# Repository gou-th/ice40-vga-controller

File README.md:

# ice40-vga-controller

A custom FPGA-based VGA controller designed for **640×480 @ 60 Hz**, implementing VGA timing generation, pixel logic and a **4-layer PCB** using the **Lattice iCE40HX1K** FPGA.

---

## Overview

This project implements a minimal yet fully functional VGA video controller without using vendor IP cores. The design follows a complete hardware development flow, starting from logic validation and RTL simulation to a manufacturable multilayer PCB.

The controller generates standard VGA sync signals and RGB video output compatible with conventional VGA displays.

---

## Architecture

The system is divided into three main functional blocks:

### VGA Timing Generation

* Horizontal and vertical pixel counters
* HSYNC and VSYNC pulse generation
* Active video region detection based on VGA timing parameters

### Pixel Generation

* RGB pixel values derived from current pixel coordinates
* Simple scrolling color-bar test pattern
* 4-bit color depth per RGB channel

### Hardware Output

* Digital RGB converted to analog VGA levels using a resistor ladder DAC
* Standard DE-15 VGA connector interface
* FPGA I/O powered at 3.3 V with proper decoupling

---

## Implementation Flow

### Logic Validation

Initial VGA timing was verified using Digital simulation software to confirm counter behavior, sync pulse timing and active display window alignment.

Reference: [`Digital`](./digital)

### RTL Design and Simulation

The design is implemented in SystemVerilog using a modular structure:

* [`vga_timing.sv`](./systemverilog/rtl/vga_timing.sv) – VGA timing and sync generation
* [`vga_pixel_gen.sv`](./systemverilog/rtl/vga_pixel_gen.sv) – RGB pixel generation
* [`vga_timing_tb.sv`](./systemverilog/sim/vga_timing_tb.sv) – Testbench for waveform-level verification

References:

* RTL: [`RTL`](./systemverilog/rtl)
* Simulation: [`Simulation & Waveform`](./systemverilog/sim)

### PCB Design

A complete 4-layer PCB was designed in KiCad to host the VGA controller.

Layer stackup:

* Top: Signal routing
* Inner 1: Ground plane
* Inner 2: Power planes
* Bottom: Signal routing

Key hardware features:

* Lattice iCE40HX1K FPGA
* Dedicated core and I/O power planes
* Local decoupling on all power pins
* VGA DAC placed close to FPGA outputs

References:

* Schematic:  [`Schematic`](./kicad/schematic)
* PCB: [`PCB`](./kicad/pcb)
* Gerbers: [`Gerber`](./kicad/gerber)

---

## 3D PCB View

---

### Folder Structure

<pre>
ice40-vga-controller/
├── digital/                # VGA timing validation using Digital simulation tool
├── systemverilog/
│   ├── rtl/                # SystemVerilog RTL source files
│   └── sim/                # Testbench and simulation files
├── kicad/
│   ├── schematic/          # Circuit schematics
│   ├── pcb/                # PCB layout files
│   └── gerber/             # Manufacturing Gerber files
└── README.md
</pre>

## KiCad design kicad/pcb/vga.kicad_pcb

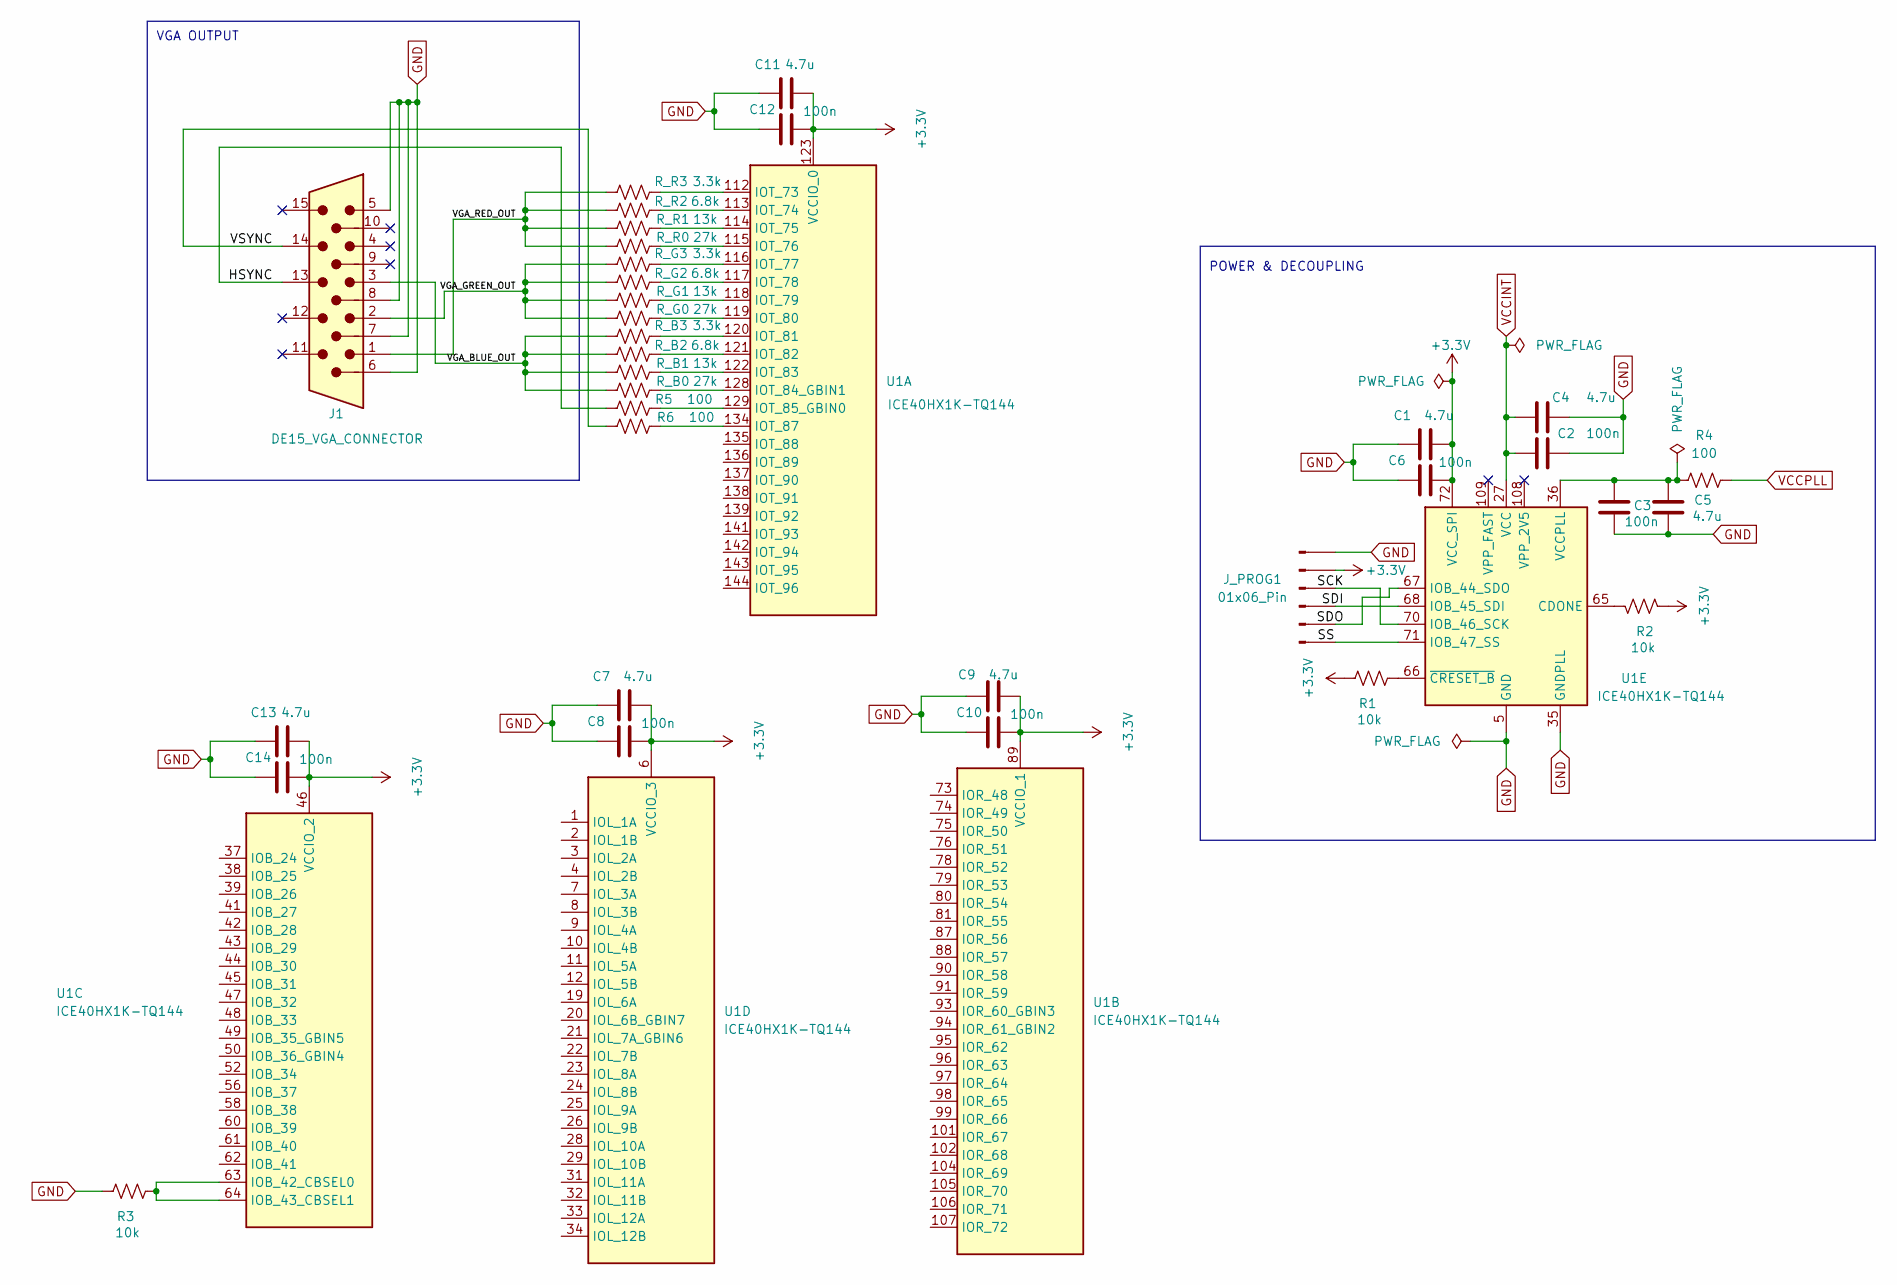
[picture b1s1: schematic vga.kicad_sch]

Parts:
C1, C4, C5, C7, C9, C11, C13: 4.7u; C_0805_2012Metric
C2, C3, C6, C8, C10, C12, C14: 100n; C_0603_1608Metric
J1: DE15_VGA_CONNECTOR; DSUB-15_Socket_Horizontal_P2.77x2.84mm_EdgePinOffset9.40mm
J_PROG1: 01x06_Pin; PinHeader_1x06_P2.54mm_Vertical
R1, R2, R3: 10k; R_0603_1608Metric
R4, R5, R6: 100; R_0603_1608Metric
R_B0: 27k; R_0603_1608Metric
R_B1: 13k; R_0603_1608Metric
R_B2: 6.8k; R_0603_1608Metric
R_B3: 3.3k; R_0603_1608Metric
R_G0: 27k; R_0603_1608Metric
R_G1: 13k; R_0603_1608Metric
R_G2: 6.8k; R_0603_1608Metric
R_G3: 3.3k; R_0603_1608Metric
R_R0: 27k; R_0603_1608Metric
R_R1: 13k; R_0603_1608Metric
R_R2: 6.8k; R_0603_1608Metric
R_R3: 3.3k; R_0603_1608Metric
U1: ICE40HX1K-TQ144; TQFP-144_20x20mm_P0.5mm

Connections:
+3.3V: C1.1, C6.1, C7.1, C8.1, C9.1, C10.1, C11.1, C12.1, C13.1, C14.1, J_PROG1.2, R1.1, R2.1, U1.6 (VCCIO_3), U1.30 (VCCIO_3), U1.46 (VCCIO_2), U1.57 (VCCIO_2), U1.72 (VCC_SPI), U1.89 (VCCIO_1), U1.100 (VCCIO_1), U1.123 (VCCIO_0), U1.133 (VCCIO_0)
/HSYNC: J1.13, R5.1
/SCK: J_PROG1.3, U1.70 (IOB_46_SCK)
/SDI: J_PROG1.4, U1.68 (IOB_45_SDI)
/SDO: J_PROG1.5, U1.67 (IOB_44_SDO)
/SS: J_PROG1.6, U1.71 (IOB_47_SS)
/VGA_BLUE_OUT: J1.3, R_B0.2, R_B1.2, R_B2.2, R_B3.2
/VGA_GREEN_OUT: J1.2, R_G0.2, R_G1.2, R_G2.2, R_G3.2
/VGA_RED_OUT: J1.1, R_R0.2, R_R1.2, R_R2.2, R_R3.2
/VSYNC: J1.14, R6.1
GND: C1.2, C2.1, C3.1, C4.1, C5.2, C6.2, C7.2, C8.2, C9.2, C10.2, C11.2, C12.2, C13.2, C14.2, J1.5, J1.6, J1.7, J1.8, J_PROG1.1, R3.1, U1.5 (GND), U1.13 (GND), U1.14 (GND), U1.35 (GNDPLL), U1.59 (GND), U1.69 (GND), U1.86 (GND), U1.103 (GND), U1.132 (GND), U1.140 (GND)
unnamed: R_R3.1, U1.112 (IOT_73)
unnamed: R_R2.1, U1.113 (IOT_74)
unnamed: R_R1.1, U1.114 (IOT_75)
unnamed: R_R0.1, U1.115 (IOT_76)
unnamed: R_G3.1, U1.116 (IOT_77)
unnamed: R_G2.1, U1.117 (IOT_78)
unnamed: R_G1.1, U1.118 (IOT_79)
unnamed: R_G0.1, U1.119 (IOT_80)
unnamed: R_B3.1, U1.120 (IOT_81)
unnamed: R_B2.1, U1.121 (IOT_82)
unnamed: R_B1.1, U1.122 (IOT_83)
unnamed: R_B0.1, U1.128 (IOT_84_GBIN1)
unnamed: R5.2, U1.129 (IOT_85_GBIN0)
unnamed: R6.2, U1.134 (IOT_87)
unnamed: R3.2, U1.63 (IOB_42_CBSEL0), U1.64 (IOB_43_CBSEL1)
unnamed: R2.2, U1.65 (CDONE)
unnamed: C3.2, C5.1, R4.1, U1.36 (VCCPLL)
unnamed: R1.2, U1.66 (~CRESET_B)
VCCINT: C2.2, C4.2, U1.27 (VCC), U1.51 (VCC), U1.92 (VCC), U1.111 (VCC)
VCCPLL: R4.2

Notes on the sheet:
VGA OUTPUT
POWER & DECOUPLING

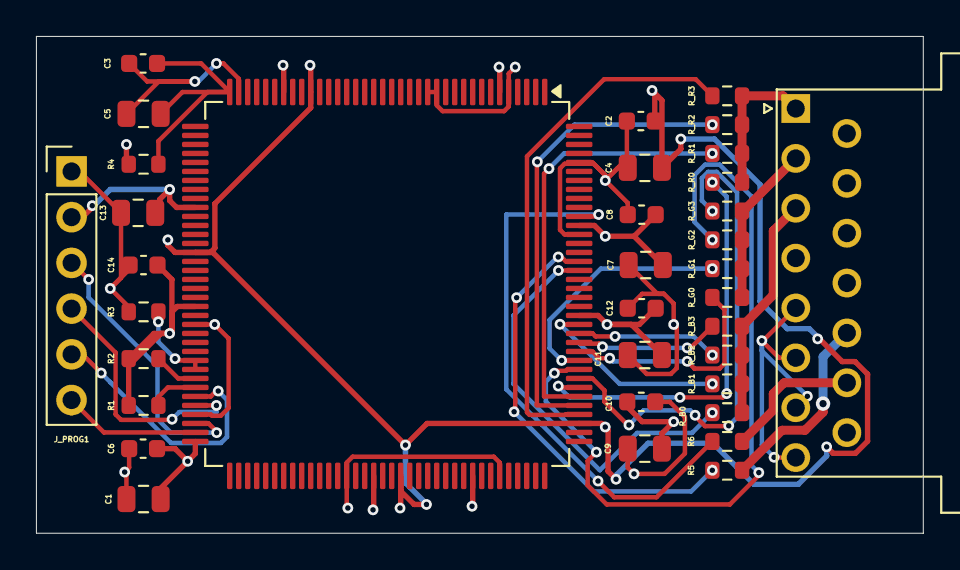
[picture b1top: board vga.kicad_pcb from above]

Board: 4 copper layers, 49.3 x 27.6 mm, 35 parts (0 on the bottom side), 30 nets.

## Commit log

2025-12-13 Create digital folder
2025-12-13 README
2025-12-13 Revise README
2026-02-10 Revised README
    Updated README
2026-02-10 Add MIT License to the project
2026-03-05 Added comments for VGA horizontal and vertical counters
    Added horizontal and vertical counter logic comments
2026-03-05 Add comments for scroll offset and color generation
